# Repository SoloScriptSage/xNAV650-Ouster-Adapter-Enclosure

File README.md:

# xNAV650 to Ouster OS1 Adapter

**Time Synchronization Interface for Precision LiDAR Mapping**

---

## 📋 Overview

This project provides a complete hardware adapter solution to interface the **OxTS xNAV650 GPS/INS** system with **Ouster OS1 LiDAR** sensors. The adapter enables precise time synchronization via PPS (Pulse Per Second) signals and NMEA data transmission, critical for accurate georeferenced point cloud generation in autonomous vehicle and mobile mapping applications.

### Why This Adapter?

The xNAV650 outputs RS232 signals at 3.3V logic levels, while the Ouster OS1 requires TTL 5V signals. This adapter bridges the gap by:

- Converting RS232 NMEA messages to TTL 5V logic
- Level-shifting PPS synchronization signals from 3.3V to 5V
- Providing stable 5V power regulation from 12V vehicle supply
- Offering a compact, ruggedized enclosure for field deployment
- Enabling plug-and-play operation with standard connectors

---

## ✨ Features

- ✅ **RS232 to TTL Conversion** - MAX3232 transceiver for NMEA data
- ✅ **PPS Signal Buffering** - 74HC125 quad buffer for 5V TTL output
- ✅ **Power Regulation** - OKI-78SR switching regulator (12V → 3.3V, 1.5A)
- ✅ **Compact Design** - 90×60×30mm enclosure fits in tight spaces
- ✅ **Standard Connectors** - Micro-D 15-pin (xNAV650), RJ45 (Ouster)
- ✅ **Visual Feedback** - Power indicator LED
- ✅ **Ethernet Pass-through** - Maintains network connectivity
- ✅ **Field-Ready** - Designed for vibration and outdoor use

---

## 🛠️ Project Components

### 📁 Repository Structure

```
xNAV650-Ouster-Adapter/
├── hardware/
│   ├── schematics/
│   │   └── XNAVOUSTER.kicad_sch      # KiCad schematic
│   ├── pcb/
│   │   └── XNAVOUSTER.kicad_pcb      # PCB layout (if available)
│   └── gerbers/                       # Manufacturing files
├── enclosure/
│   ├── 3d-models/
│   │   ├── bottom.stl                 # 3D printable base
│   │   ├── lid.stl                    # 3D printable lid
│   │   └── complete.step              # Editable CAD file
│   └── drilling-template.pdf          # For off-the-shelf enclosures
├── docs/
│   ├── BOM.md                         # Bill of Materials
│   ├── assembly-guide.md              # Step-by-step assembly
│   └── user-manual.pdf                # Operation instructions
├── firmware/                          # (Future: microcontroller config)
├── examples/                          # Sample configurations
└── README.md                          # This file
```

---

## 🔧 Hardware Specifications

### Electrical

| Parameter | Value |
|-----------|-------|
| **Input Voltage** | 12V DC ±10% (10.8V - 13.2V) |
| **Current Draw** | 200-300mA typical |
| **Output Voltage** | 5V TTL (Ouster), 3.3V internal logic |
| **NMEA Baud Rate** | 115200 bps (configurable) |
| **PPS Signal** | 5V TTL, 1Hz, <1μs rise time |
| **Connectors** | Micro-D 15 (input), RJ45 (output) |

### Mechanical

| Parameter | Value |
|-----------|-------|
| **External Dimensions** | 90×60×30mm |
| **Weight** | ~120g (with PCB) |
| **Enclosure Material** | ABS/PETG (3D print) or polycarbonate |
| **Operating Temperature** | -20°C to +70°C |
| **Mounting** | 4× M3 standoffs |

### Key Components

- **U2** - MAX3232CPE: RS232 ↔ TTL transceiver
- **U3** - OKI-78SR-3.3/1.5-W36-C: Buck converter (12V→3.3V)
- **U4** - 74HC125N: Quad 3-state buffer for signal conditioning
- **C1-C5** - 100µF electrolytic capacitors for filtering
- **J1** - DC barrel jack (12V input)
- **J2** - 15-pin Micro-D connector (xNAV650 interface)
- **J4** - RJ45 shielded connector (Ouster interface)

---

## 📦 Bill of Materials (BOM)

Total estimated cost: **$75-160 USD** (prototype quantities)

### Core Components

| Ref | Qty | Part Number | Description | Est. Price |
|-----|-----|-------------|-------------|------------|
| U2 | 1 | MAX3232CPE+ | RS232 Transceiver | $3-5 |
| U3 | 1 | OKI-78SR-3.3/1.5-W36-C | DC-DC Converter | $6-10 |
| U4 | 1 | 74HC125N | Quad Buffer | $0.50-1 |
| J2 | 1 | Micro-D 15-pin Female | xNAV650 Connector | $8-15 |
| J4 | 1 | RJ45 Shielded | Ouster Connector | $2-5 |
| C1-C5 | 5 | 100µF/16V | Electrolytic Caps | $3-5 |
| R1-R2 | 2 | 100Ω | Resistors | $0.50 |

**📄 [Complete BOM with part numbers →](docs/BOM.md)**

### Where to Buy

- **Mouser Electronics** - https://www.mouser.com
- **DigiKey** - https://www.digikey.com
- **Farnell** - https://www.farnell.com
- **LCSC** (for Asia) - https://www.lcsc.com

---

## 🚀 Quick Start Guide

### Prerequisites

Before starting, ensure you have:

- [ ] xNAV650 GPS/INS system with user cable
- [ ] Ouster OS1 LiDAR sensor
- [ ] 12V DC power supply (vehicle or bench supply)
- [ ] Basic soldering equipment
- [ ] Multimeter for testing

### Assembly Overview

1. **Order Components** - Use BOM to order parts from suppliers
2. **PCB Fabrication** - Upload gerbers to PCB manufacturer (JLCPCB, PCBWay, etc.)
3. **Enclosure Preparation** - 3D print or purchase Hammond 1591XXSSBK
4. **PCB Assembly** - Solder all components following assembly guide
5. **Enclosure Integration** - Mount connectors and install PCB
6. **Testing** - Verify voltages and signal integrity
7. **Deployment** - Connect to xNAV650 and Ouster

**📖 [Detailed Assembly Instructions →](docs/assembly-guide.md)**

---

## 🔌 Connection Diagram

```
┌─────────────┐         ┌──────────────┐         ┌─────────────┐
│  xNAV650    │         │   Adapter    │         │  Ouster OS1 │
│  GPS/INS    │─15pin──▶│   PCB        │──RJ45──▶│   LiDAR     │
│             │         │              │         │             │
│ • RS232 TX  │────────▶│ MAX3232      │────────▶│ NMEA (TTL)  │
│ • PPS 3.3V  │────────▶│ 74HC125      │────────▶│ PPS (5V)    │
│ • Ethernet  │────────▶│ Pass-through │────────▶│ Ethernet    │
└─────────────┘         └──────────────┘         └─────────────┘
                              ▲
                              │ 12V DC
                        ┌─────┴─────┐
                        │  Vehicle  │
                        │   Power   │
                        └───────────┘
```

### Pin Mapping

**xNAV650 (J2 - Micro-D 15) → Adapter:**
- Pin 1-2, 14-15: Supply+ / Supply- (12V)
- Pin 3: Serial RX (RS232)
- Pin 4: Serial TX (RS232) → to MAX3232
- Pin 12: PPS (3.3V isolated) → to 74HC125
- Pin 5-8: Ethernet (ERX+/-, ETX+/-) → pass-through

**Adapter → Ouster OS1 (J4 - RJ45):**
- Pins 1-2, 3-6, 7-8: Ethernet (standard T568B)
- Pin 4-5: NMEA_TX (TTL 5V from MAX3232)
- Custom pin: SYNC_PULSE_IN (PPS 5V from 74HC125)

**💡 Tip:** Refer to Ouster OS1 hardware integration guide for exact pinout

---

## ⚙️ Configuration

### xNAV650 Configuration (NAVconfig)

1. **Enable NMEA Output:**
   - Open NAVconfig
   - Navigate to: `Hardware Setup > LiDAR Scanner`
   - Select: Velodyne VLP-16 (or custom)
   - Set NMEA Output: **Serial** or **Ethernet** (choose serial for this adapter)
   - Baud Rate: **115200 bps**

2. **Configure PPS Signal:**
   - Navigate to: `Interfaces > PPS/Triggers`
   - PPS Active Edge: **Falling** (check Ouster requirements)
   - PPS Source: **GNSS Receiver**

3. **Save and Upload:**
   - Save configuration
   - Upload to xNAV650 via ethernet
   - Reboot unit

### Ouster OS1 Configuration

Access Ouster web interface (default: `http://os1-XXXX.local/`):

1. **Set Time Sync Mode:**
   ```bash
   TIME_SYNC_MODE = "PTP" or "NMEA"
   ```
   For this adapter, use: **NMEA + PPS**

2. **Configure NMEA:**
   ```bash
   NMEA_IN_POLARITY = "ACTIVE_HIGH"  # or ACTIVE_LOW, test both
   NMEA_BAUD_RATE = 115200
   ```

3. **Verify Synchronization:**
   - Check web interface: `Status > Time Sync`
   - Should show: "Synchronized" with GPS time

**📚 [Official Ouster Integration Guide](https://www.oxts.com/wp-content/uploads/2025/03/Ouster-Hardware-Integration-Guide_compressed.pdf)**

---

## 🧪 Testing & Validation

### Pre-Deployment Checks

**1. Power Test:**
```
□ Connect 12V power supply
□ Verify LED illuminates (green)
□ Measure 3.3V at U3 output pin
□ Measure 5V at MAX3232 VCC pin
□ Check U3 temperature (<60°C)
```

**2. Signal Integrity Test:**
```
□ Connect oscilloscope to PPS output
□ Verify 1Hz square wave, 5V amplitude
□ Check rise time <1μs
□ Measure NMEA TX voltage: ~5V high, ~0V low
```

**3. Communication Test:**
```
□ Connect xNAV650 and power on
□ Use USB-TTL adapter to monitor NMEA output
□ Should see NMEA sentences at 115200 baud
□ Example: $GPRMC,123519,A,4807.038,N,01131.000,E...
```

**4. Integration Test:**
```
□ Connect complete system (xNAV + Adapter + Ouster)
□ Power on in sequence
□ Check Ouster web interface for sync status
□ Verify point cloud timestamps match GPS time
```

### Troubleshooting

| Issue | Possible Cause | Solution |
|-------|---------------|----------|
| No LED | No 12V power / blown fuse | Check power supply, replace fuse |
| LED on, no NMEA | MAX3232 not configured | Check solder joints, verify xNAV config |
| NMEA works, no PPS | 74HC125 issue | Verify PPS input from xNAV, check buffer |
| Ouster not syncing | Wrong polarity | Try inverting PPS_IN_POLARITY setting |
| Intermittent operation | Loose connections | Re-solder connectors, check crimps |

---

## 📐 Enclosure Options

### Option 1: 3D Printing (Recommended)

**Files:** `enclosure/3d-models/`

**Materials:**
- **PETG** (recommended) - Strong, temperature resistant
- **ABS** - Good for outdoor use
- **Nylon** - Maximum durability

**Print Settings:**
- Layer height: 0.2mm
- Infill: 30-40%
- Supports: Yes (for mounting holes)
- Print time: ~4-6 hours

**📥 [Download STL Files →](enclosure/3d-models/)**

### Option 2: Off-the-Shelf Enclosure

**Recommended:** Hammond 1591XXSSBK
- Dimensions: 85×56×25mm
- Material: ABS, IP54 rated
- Price: $8-12 USD
- Requires drilling holes (template provided)

**📄 [Drilling Template PDF →](enclosure/drilling-template.pdf)**

### Option 3: CNC Machining

For production runs or harsh environments:
- Material: Aluminum 6061-T6
- Anodized finish for corrosion resistance
- Cost: $40-80 per unit (qty 10+)

---

## 🎯 Use Cases

### Mobile Mapping
- Survey vehicles with synchronized LiDAR and GPS
- Accurate georeferencing of point clouds
- Highway infrastructure inspection

### Autonomous Vehicles
- Sensor fusion with precise timing
- SLAM (Simultaneous Localization and Mapping)
- Real-time navigation systems

### Robotics
- Mobile robots requiring GPS/LiDAR integration
- Agricultural automation
- Warehouse and industrial AGVs

### Research & Development
- Academic research platforms
- Algorithm development for autonomous systems
- Multi-sensor calibration studies

---

## 📚 Documentation

- **[Bill of Materials (BOM)](docs/BOM.md)** - Complete component list with part numbers
- **[Assembly Guide](docs/assembly-guide.md)** - Step-by-step construction
- **[User Manual](docs/user-manual.pdf)** - Operation and maintenance
- **[Hardware Schematic](hardware/schematics/XNAVOUSTER.kicad_sch)** - KiCad source
- **[3D Models](enclosure/3d-models/)** - STL and STEP files

### External References

- [xNAV650 Hardware Manual](https://www.datrontechnology.co.uk/wp-content/uploads/2021/03/xNAV650-manual-210311.pdf)
- [Ouster OS1 Documentation](https://ouster.com/downloads)
- [OxTS-Ouster Integration Guide](https://www.oxts.com/wp-content/uploads/2025/03/Ouster-Hardware-Integration-Guide_compressed.pdf)
- [MAX3232 Datasheet (TI)](https://www.ti.com/product/MAX3232)
- [OKI-78SR Datasheet (Murata)](https://www.murata.com/products/productdata/8807031734302/oki-78sr.pdf)

---

## 🤝 Contributing

Contributions are welcome! Here's how you can help:

### Ways to Contribute

- 🐛 **Report bugs** - Open an issue with details
- 💡 **Suggest features** - Share your ideas for improvements
- 📖 **Improve documentation** - Fix typos, add examples
- 🔧 **Hardware improvements** - PCB layout optimizations, component alternatives
- 📦 **Alternative enclosures** - Share your designs
- 🧪 **Testing** - Validate in different environments

### Development Workflow

1. Fork the repository
2. Create a feature branch (`git checkout -b feature/amazing-improvement`)
3. Commit your changes (`git commit -am 'Add amazing improvement'`)
4. Push to the branch (`git push origin feature/amazing-improvement`)
5. Open a Pull Request

### Code of Conduct

Be respectful, constructive, and collaborative. This is an open-source hardware project intended to help the community.

---

## 📄 License

This project is licensed under the **MIT License** - see [LICENSE](LICENSE) file for details.

### What this means:
- ✅ Commercial use allowed
- ✅ Modification allowed
- ✅ Distribution allowed
- ✅ Private use allowed
- ⚠️ No warranty provided
- ⚠️ Author not liable

**Attribution appreciated but not required!**

---

## 🙋 Support & Contact

### Getting Help

- **Issues:** Open an issue on GitHub for bugs or questions
- **Discussions:** Use GitHub Discussions for general questions
- **Email:** hirchukv@gmail.com

### Community

- **GitHub:** [@SoloScriptSage](https://github.com/SoloScriptSage)
- **Project Website:** [View interactive demo →](https://soloscriptsage.github.io/xnav-adapter.html)

### Commercial Support

For custom designs, integration services, or bulk orders:
- Contact: hirchukv@gmail.com
- Available for consulting on similar GPS/LiDAR projects

---

## 🏆 Acknowledgments

- **OxTS** - xNAV650 documentation and support
- **Ouster** - LiDAR hardware integration guides
- **Open Source Community** - KiCad, FreeCAD, and related tools
- **Contributors** - Everyone who improves this project

---

## 📊 Project Status

- [x] Initial schematic design
- [x] PCB layout
- [x] BOM compilation
- [x] 3D enclosure design
- [x] Assembly documentation
- [ ] Prototype testing
- [ ] Production manufacturing
- [ ] Field deployment validation
- [ ] Firmware development (future)
- [ ] Web configuration interface (future)

**Current Version:** 1.0 (Beta)  
**Last Updated:** November 2025

---

## 🔮 Future Improvements

### Planned Features

- [ ] **Onboard microcontroller** - ESP32 for configuration via WiFi
- [ ] **OLED display** - Status information and diagnostics
- [ ] **Data logging** - SD card for timestamp verification
- [ ] **Multiple LiDAR support** - Switch between Ouster/Velodyne/Hesai
- [ ] **Galvanic isolation** - Full isolation for harsh environments
- [ ] **Reverse power protection** - TVS diodes and polarity protection
- [ ] **Automotive connectors** - Deutsch or Amphenol for vibration resistance

### Version Roadmap

- **v1.0** - Current release (basic functionality)
- **v1.1** - Improved power filtering, EMI reduction
- **v2.0** - Microcontroller integration, web interface
- **v3.0** - Multi-LiDAR support, advanced diagnostics

---

## 💬 FAQ

**Q: Can I use this with other LiDAR brands?**  
A: Yes, with modifications. Most LiDARs accept similar NMEA+PPS inputs. Check voltage levels and pinouts.

**Q: Does this work with single-antenna xNAV systems?**  
A: Yes, PPS and NMEA work identically on single and dual-antenna configurations.

**Q: What's the expected accuracy of time synchronization?**  
A: PPS provides <1μs timing accuracy. Overall system accuracy depends on xNAV650 GPS lock quality.

**Q: Can I power the Ouster from this adapter?**  
A: No, this only provides signal conversion. Ouster requires separate 12-24V power supply.

**Q: Is PCB assembly service available?**  
A: Not officially, but you can use services like JLCPCB or PCBWay with provided gerbers.

**Q: What about CE/FCC certification?**  
A: This is a development tool. For commercial products, you'll need proper certification.

---

## 📸 Gallery

*Coming soon: Photos of assembled units, field deployments, and point cloud results*

---

**⭐ If this project helps you, please consider starring the repository!**

---

**Made with ⚡ by [Vladyslav Hirchuk](https://github.com/SoloScriptSage)**  
*Open Hardware for the Robotics Community*

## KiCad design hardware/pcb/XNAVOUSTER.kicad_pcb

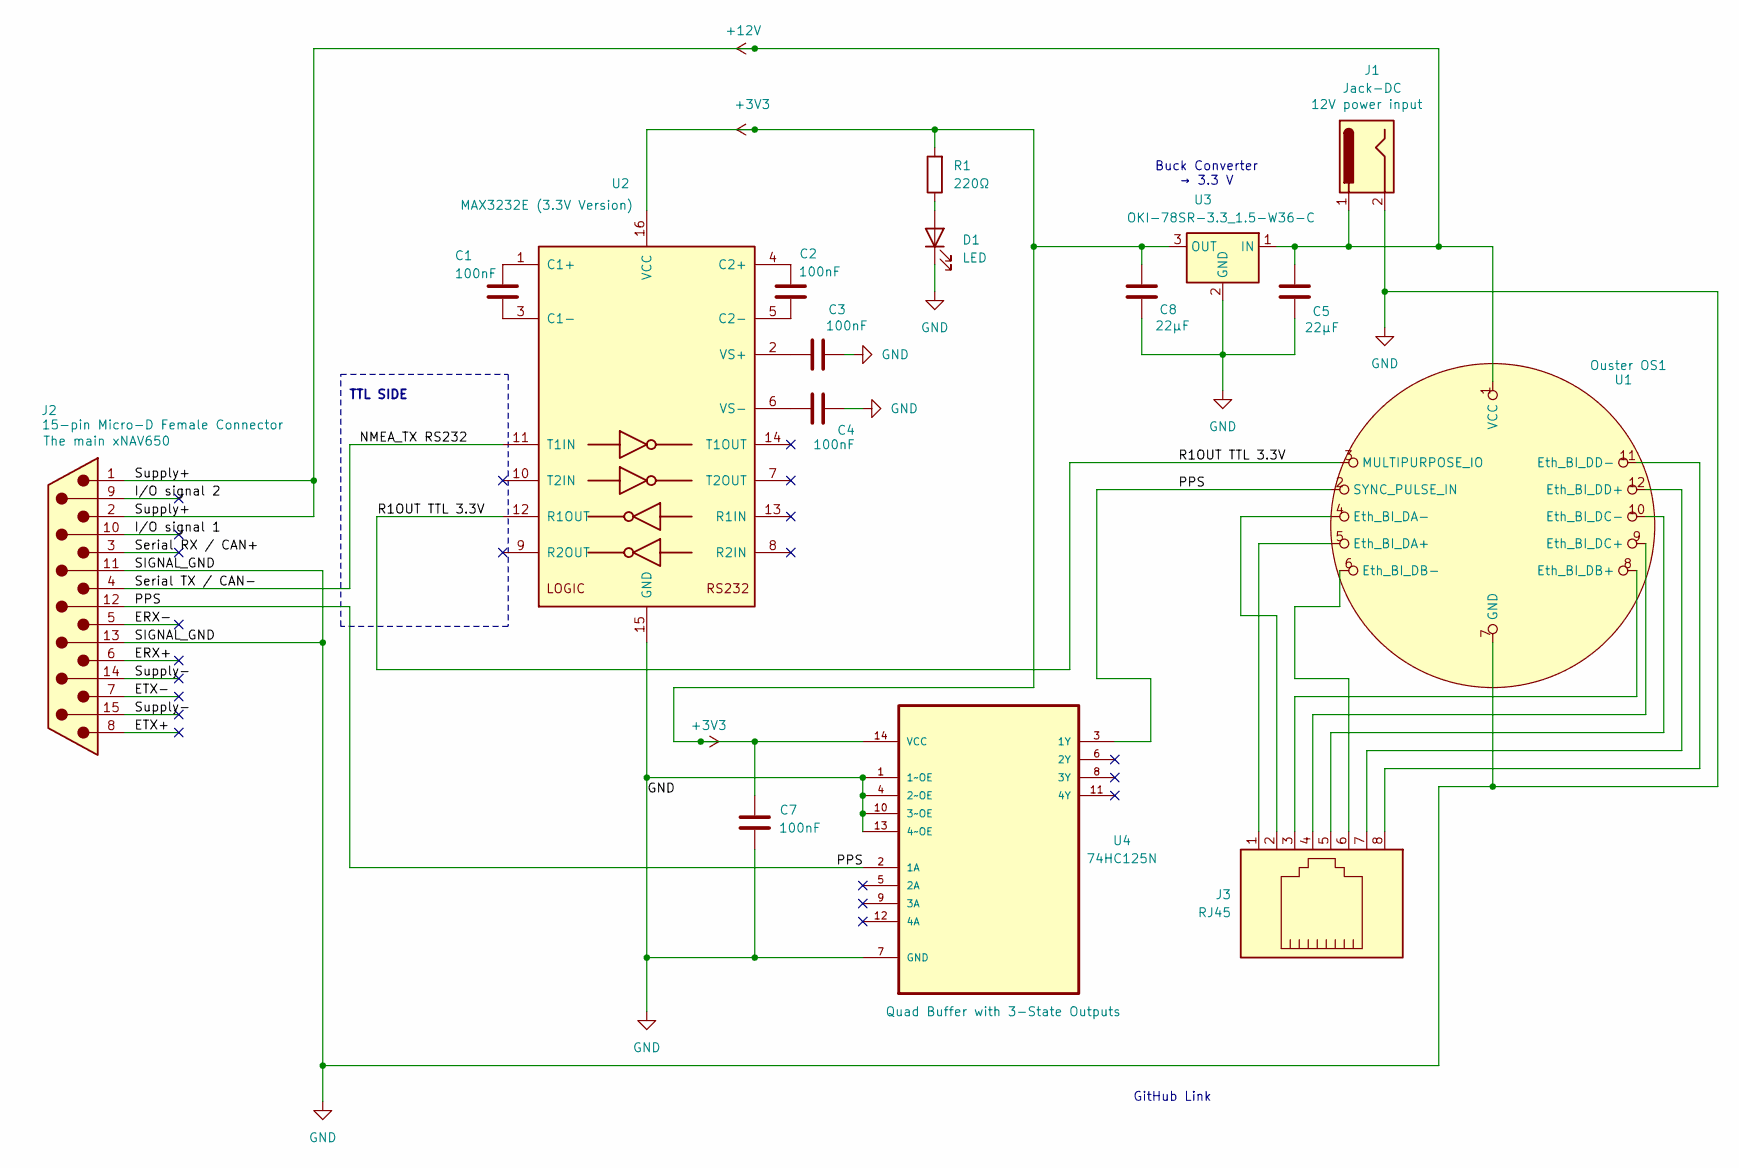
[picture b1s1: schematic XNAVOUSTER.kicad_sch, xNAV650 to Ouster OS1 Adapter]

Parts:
C1, C2, C3, C4: 100nF; C_0805_2012Metric
C5, C8: 22µF; CP_Radial_D6.3mm_P2.50mm
C7: 100nF; C_Disc_D3.0mm_W2.0mm_P2.50mm
D1: LED; LED_D3.0mm
J1: Jack-DC; BarrelJack_Horizontal
J2: 15-pin Micro-D Female Connector; DSUB-15_Pins_Horizontal_P2.77x2.84mm_EdgePinOffset7.70mm_Ho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
J3: RJ45; RJ45_Amphenol_54602-x08_Horizontal
R1: 220Ω; R_Axial_DIN0207_L6.3mm_D2.5mm_P7.62mm_Horizontal
U1: Ouster OS1; AMPHENOL_43-02742
U2: MAX3232E (3.3V Version); DIP-16_W7.62mm
U3: OKI-78SR-3.3_1.5-W36-C; Converter_DCDC_Murata_OKI-78SR_Vertical
U4: 74HC125N; SOIC-14; MPN 74HC125N

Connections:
+3V3: C7.1, C8.2, R1.2, U2.16 (VCC), U3.3 (OUT), U4.14 (VCC)
+12V: C5.2, J1.1, J2.1, J2.2, U1.1 (VCC), U3.1 (IN)
/ERX+: J2.6
/ERX−: J2.5
/ETX+: J2.8
/ETX-: J2.7
/I/O signal 1: J2.10
/I/O signal 2: J2.9
/NMEA_TX RS232: J2.4, U2.11 (T1IN)
/PPS: J2.12, U1.2 (SYNC_PULSE_IN), U4.2 (1A), U4.3 (1Y)
/R1OUT TTL 3.3V: U1.3 (MULTIPURPOSE_IO), U2.12 (R1OUT)
/Serial RX / CAN+: J2.3
/Supply−: J2.14, J2.15
GND: C3.2, C4.2, C5.1, C7.2, C8.1, D1.1 (K), J1.2, J2.11 (P111), J2.13, U1.7 (GND), U2.15 (GND), U3.2 (GND), U4.1 (1~OE), U4.4 (2~OE), U4.7 (GND), U4.10 (3~OE), U4.13 (4~OE)
unnamed: D1.2 (A), R1.1
unnamed: J3.1, U1.5 (Eth_BI_DA+)
unnamed: J3.2, U1.4 (Eth_BI_DA-)
unnamed: J3.3, U1.8 (Eth_BI_DB+)
unnamed: J3.6, U1.6 (Eth_BI_DB-)
unnamed: J3.4, U1.9 (Eth_BI_DC+)
unnamed: J3.5, U1.10 (Eth_BI_DC-)
unnamed: J3.7, U1.12 (Eth_BI_DD+)
unnamed: J3.8, U1.11 (Eth_BI_DD-)
unnamed: C1.1, U2.1 (C1+)
unnamed: C1.2, U2.3 (C1-)
unnamed: C2.1, U2.4 (C2+)
unnamed: C2.2, U2.5 (C2-)
unnamed: C3.1, U2.2 (VS+)
unnamed: C4.1, U2.6 (VS-)

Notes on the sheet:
TTL SIDE
GitHub Link
Buck Converter → 3.3 V

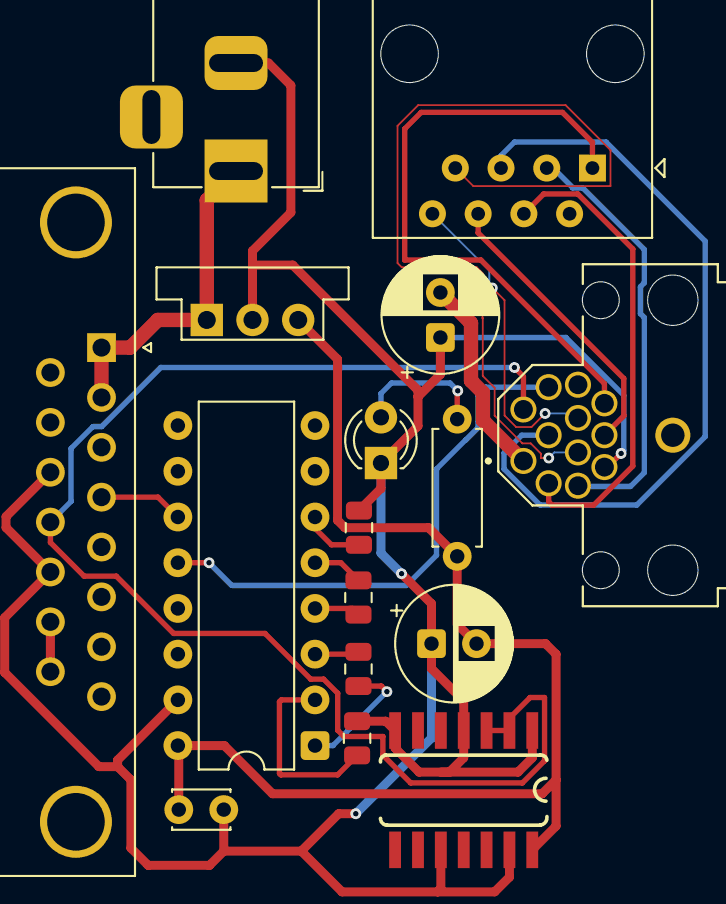
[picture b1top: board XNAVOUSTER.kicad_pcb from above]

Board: 2 copper layers, 16 parts (0 on the bottom side), 22 nets.

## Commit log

2025-11-14 Add Bill of Materials for xNAV650 to Ouster Adapter
    Added a detailed Bill of Materials (BOM) for the xNAV650 to Ouster OS1-128 Adapter, including components, descriptions, prices, and suppliers.
2025-11-14 Rename bom.csv to bom.md
2025-11-17 Create README.md for project documentation
    Add detailed README for xNAV650 to Ouster OS1 Adapter project, including overview, features, specifications, assembly instructions, and usage guidelines.
2025-11-17 Update contact email and project website link
2025-11-17 Revise BOM for xNAV650 to Ouster OS1 Adapter
    Updated revision details, component values, and specifications in the Bill of Materials. Added new components and clarified design notes for improved performance and assembly.
2025-11-22 Rename stls/lid.stl to enclosure/3d-models/lid.stl
2025-11-22 Rename stls/main.stl to enclosure/3d-models/bottom.stl
2025-11-22 Rename XNAVOUSTER.kicad_pcb to hardware/pcb/XNAVOUSTER.kicad_pcb
2025-11-22 Rename XNAVOUSTER.kicad_sch to hardware/schematics/XNAVOUSTER.kicad_sch
2025-11-22 Rename bom.md to docs/bom.md
2025-11-22 Rename hardware/gerber.zip to hardware/gerbers/gerber.zip
2025-11-22 Create s

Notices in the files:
README.md:
License: MIT
